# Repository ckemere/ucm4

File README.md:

# CM4-uSAW

Raspberry Pi Compute Module 4 micro carrier board with a multimodal Sensor Array and Wireless (uSAW) battery operation.

# Features

- Dual-camera inputs
- 9-axis IMU
- Stereo microphones
- GNSS module header (ZED GNSS)
- Stemma/QUIIC connector
- Power management
  - Battery charging & discharging
  - Fuel gauge
  - USB-C or L-ion power source
- SD card carrier
- UART Extension pins
- support for both Lite and eMMC variants of CM4
- USB C for power and USB 2.0 data transfer
- USB-OTG support

# Table of contents

1. [Sensors](sensors.md)

# License

This work is licensed under a [Creative Commons Attribution 4.0 International License][cc-by].

You can use it for anything as long as you preserve license file and author information in source distribution and authorship information on PCB. Derived work should mention original author in same locations as this repository.

[![CC BY 4.0][cc-by-image]][cc-by]

[cc-by]: http://creativecommons.org/licenses/by/4.0/
[cc-by-image]: https://i.creativecommons.org/l/by/4.0/88x31.png

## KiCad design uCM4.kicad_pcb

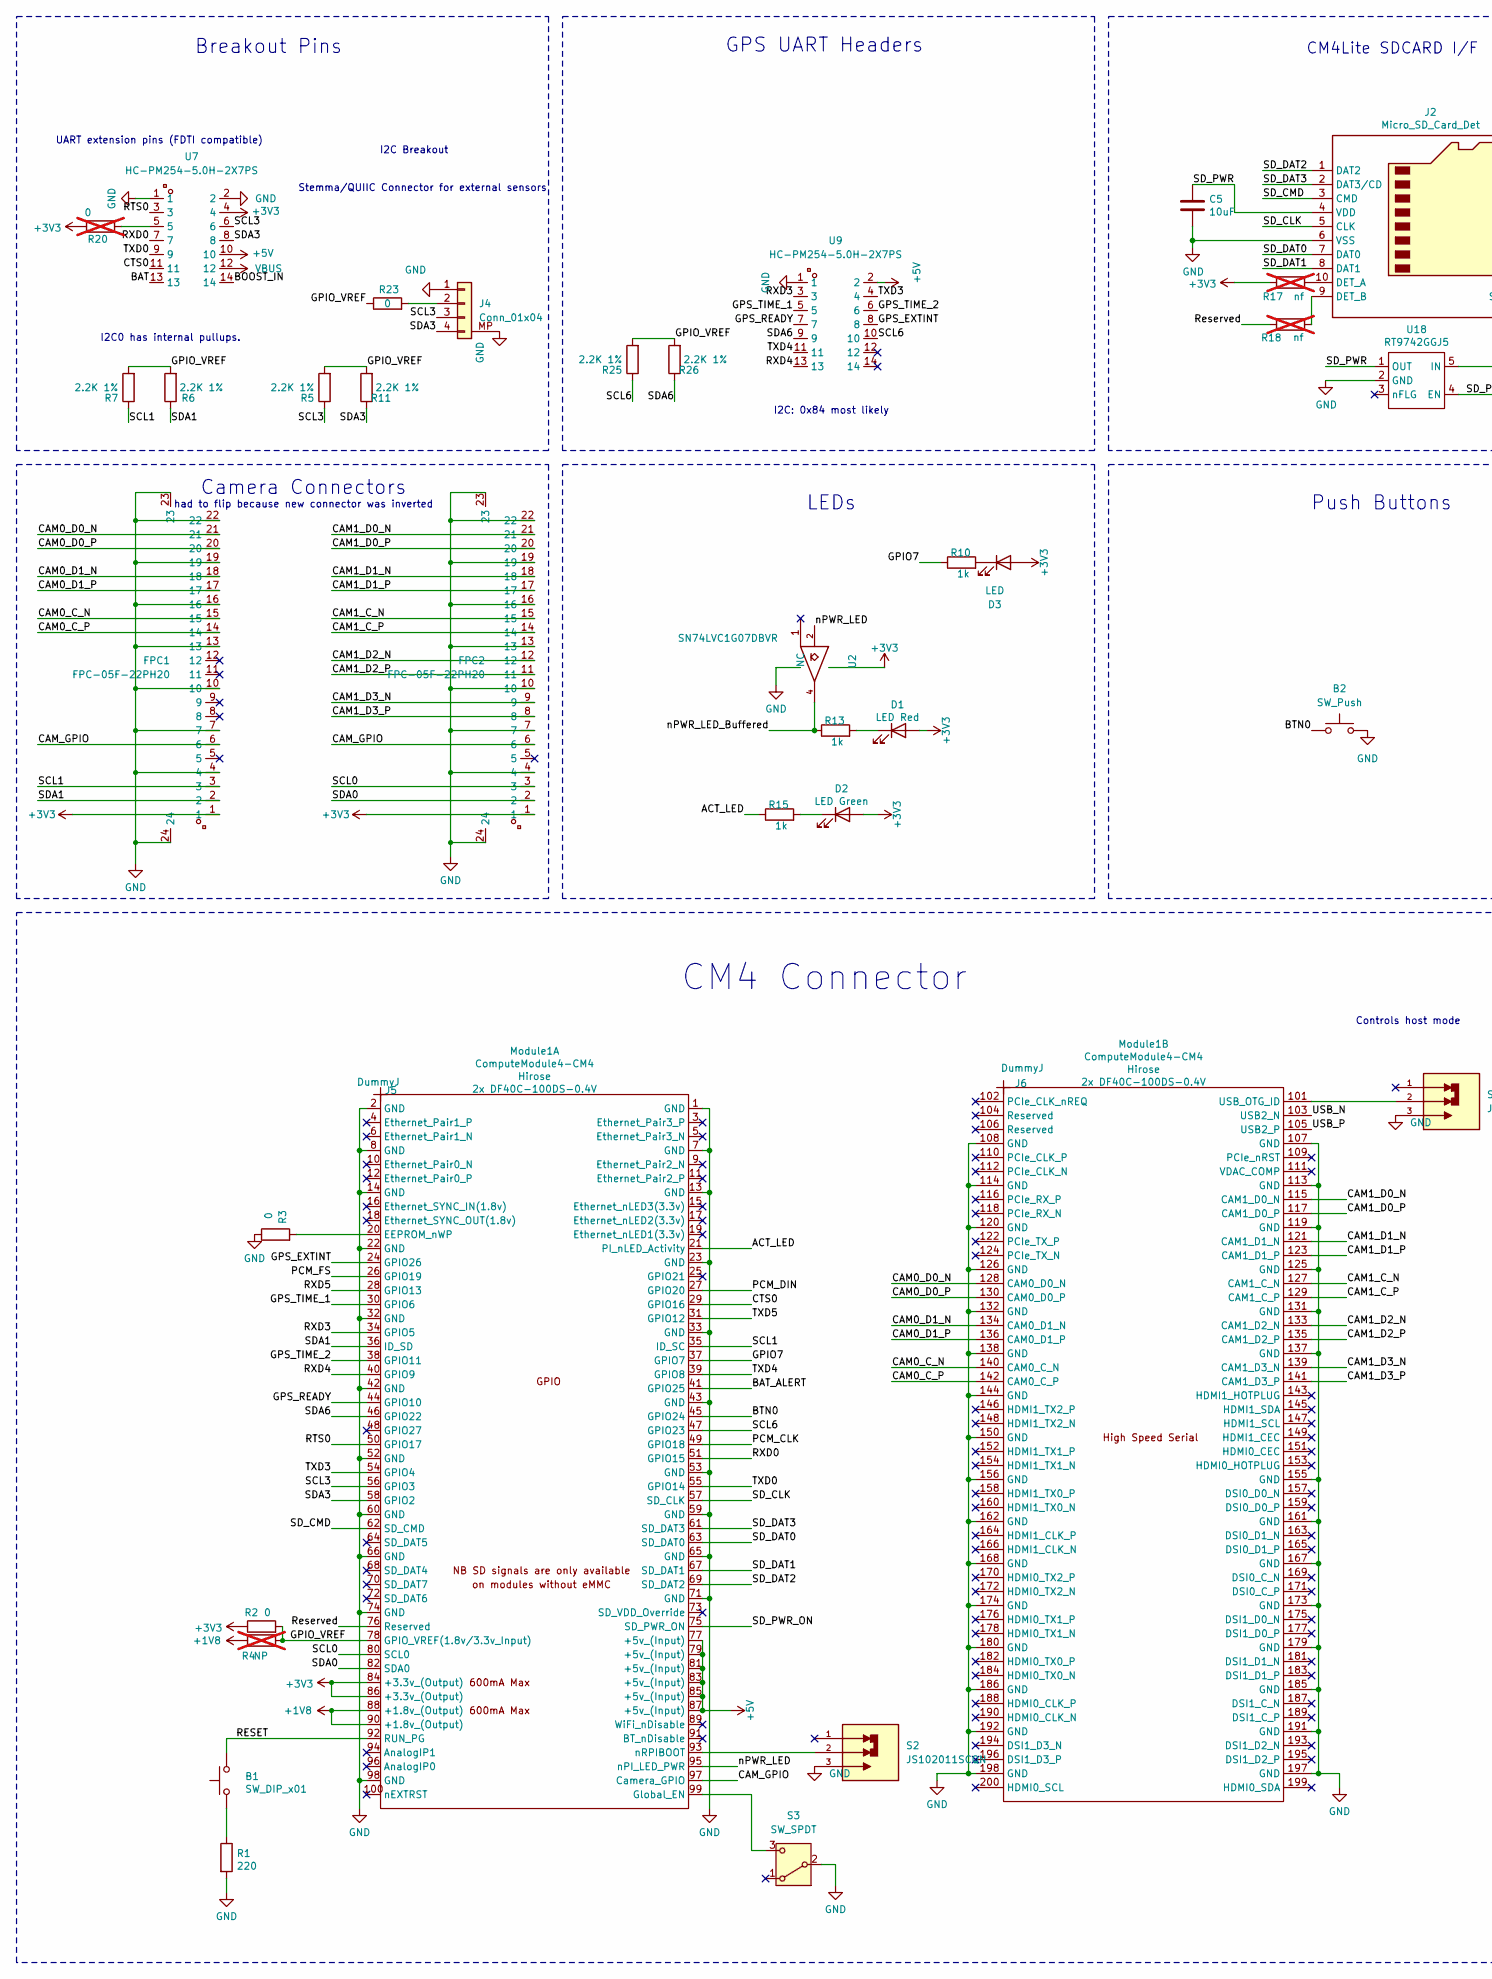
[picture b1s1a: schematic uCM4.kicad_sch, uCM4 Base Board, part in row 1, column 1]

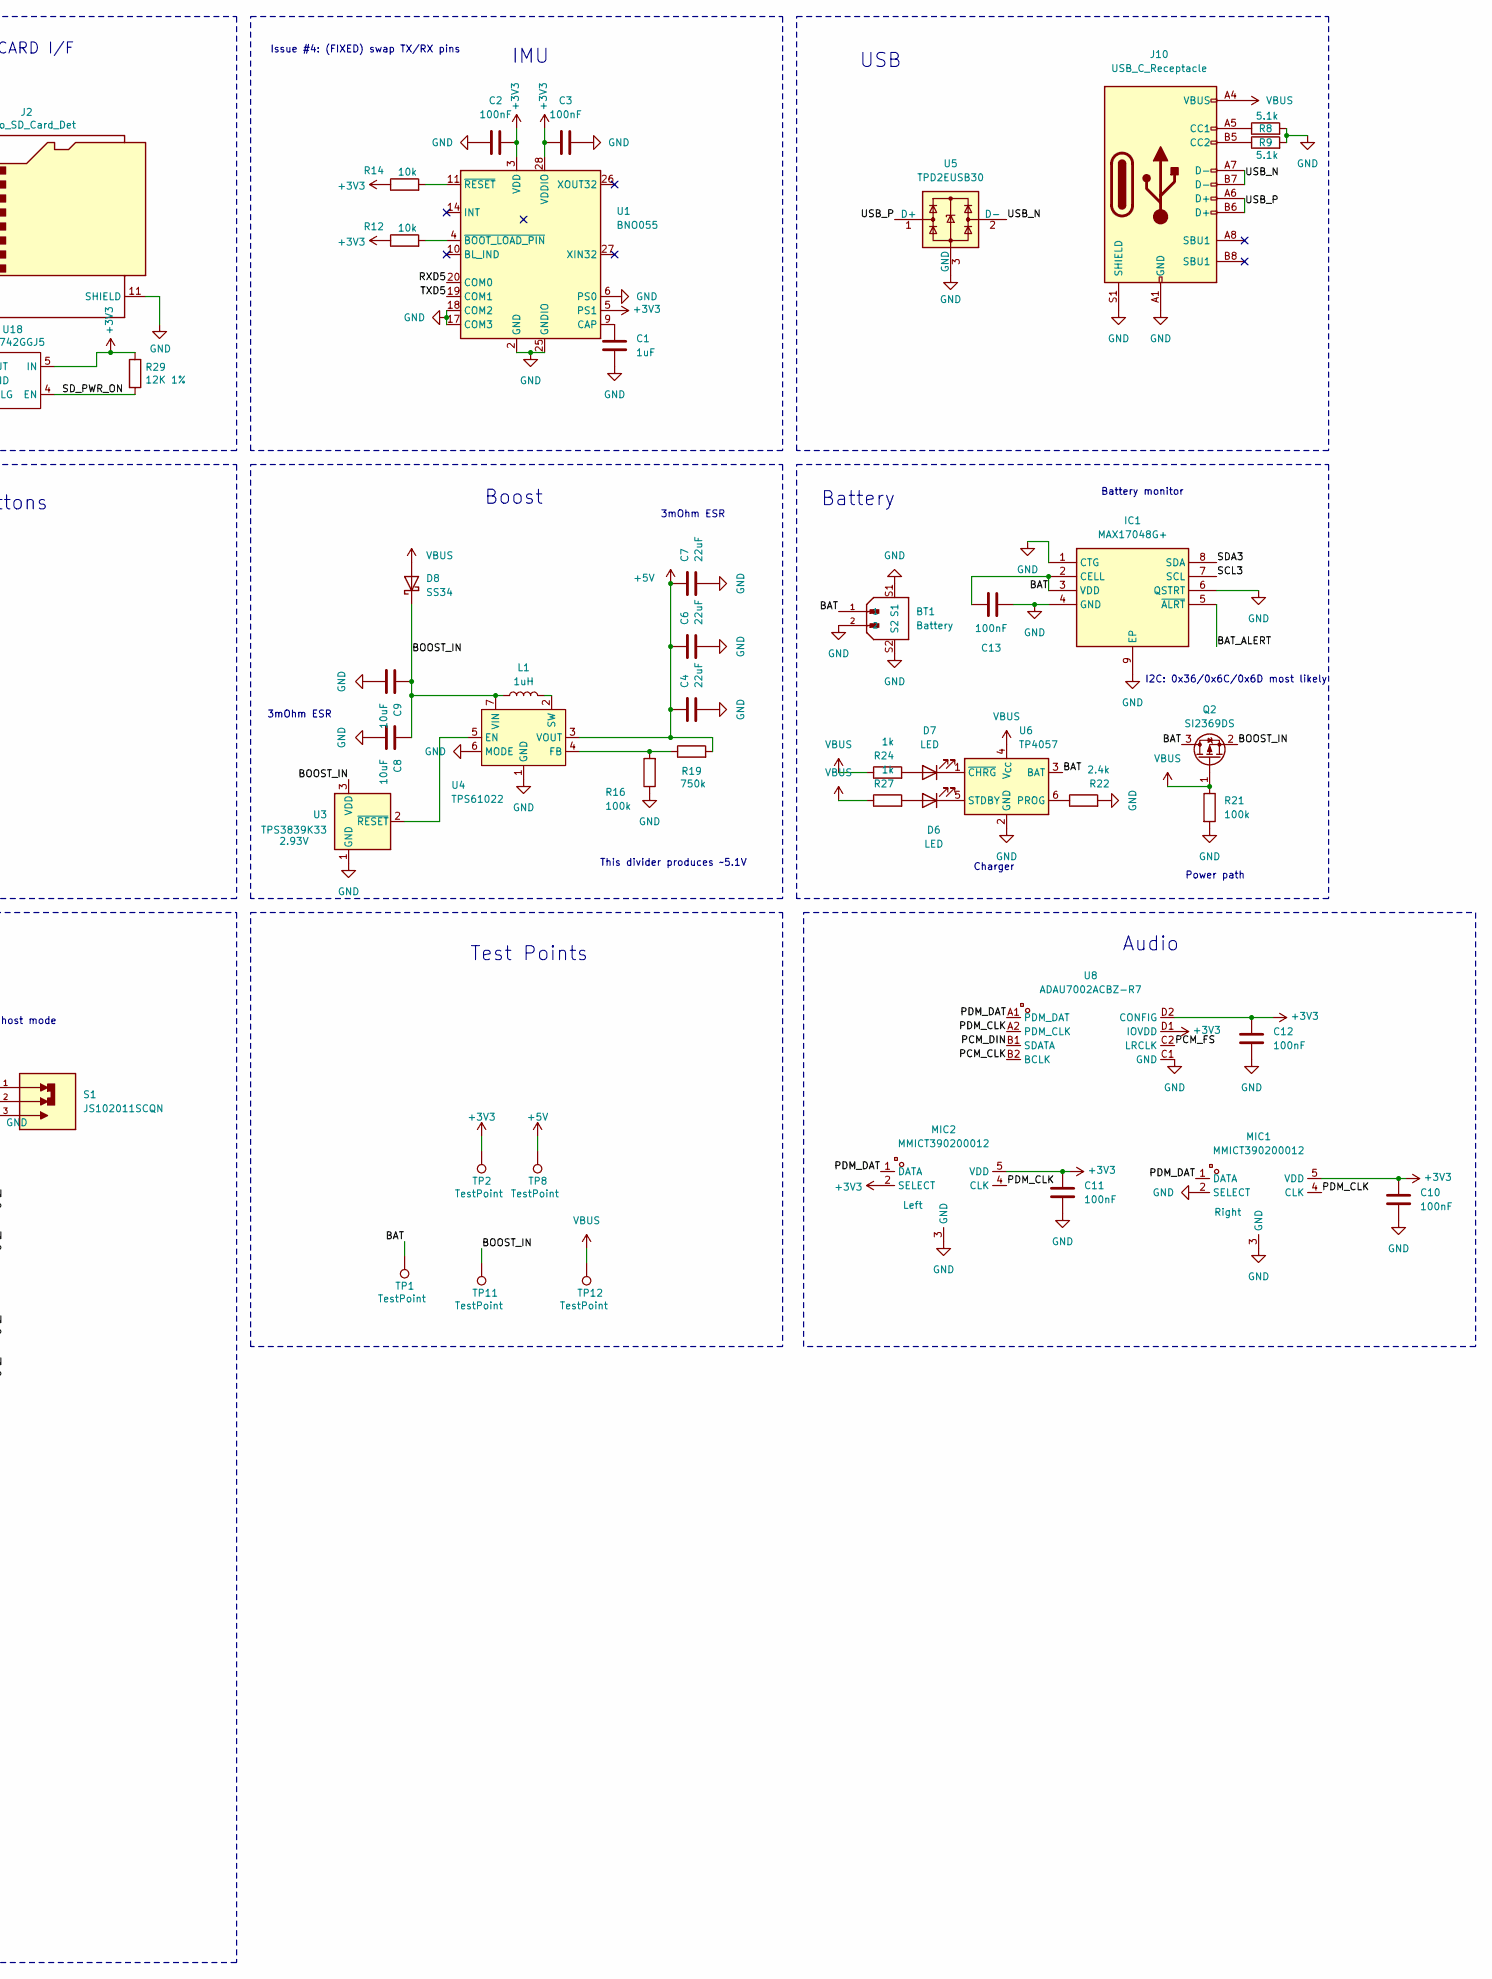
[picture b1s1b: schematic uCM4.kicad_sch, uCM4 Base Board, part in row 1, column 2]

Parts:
B1: SW_DIP_x01; PTS840_PM_SMTR_LFS; LCSC Part # C221907
B2: SW_Push; PTS840_PM_SMTR_LFS; LCSC Part # C221907
BT1: Battery; JST_B2B-PH-SM4-TB; PARTREV N/A; LCSC Part # C2763702
C1: 1uF; C_0402_1005Metric; LCSC Part # C14445
C2, C3, C10, C11, C12, C13: 100nF; C_0402_1005Metric; LCSC Part # C1525
C4, C6, C7: 22uF; C_1206_3216Metric; LCSC Part # C12891
C5: 10uF; C_0603_1608Metric; Part Description 10uF 10% 10V Ceramic Capacitor X7R 0805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; LCSC Part # C19702
C8, C9: 10uF; C_0603_1608Metric; LCSC Part # C19702
D1: LED Red; LED_0402_1005Metric; LCSC Part # C264407
D2: LED Green; LED_0402_1005Metric; LCSC Part # C5123485
D3, D6: LED; LED_0402_1005Metric; LCSC Part # C5123485
D7: LED; LED_0402_1005Metric; LCSC Part # C264407
D8: SS34; D_SMA; LCSC Part # C727059
FPC1, FPC2: FPC-05F-22PH20; FPC-SMD_22P-P0.50_FPC-05F-22PH20; LCSC Part C2856804
IC1: MAX17048G+; SON50P200X200X80-9N-D; Manufacturer_Part_Number MAX17048G+; Mouser Part Number 700-MAX17048G+
J2: Micro_SD_Card_Det; SDCARD_MOLEX_503398-1892; Part Description 9 (8 + 1) Position Card Connector micro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; LCSC Part # C428492
J4: Conn_01x04; JST_SH_BM04B-SRSS-TB_1x04-1MP_P1.00mm_Vertical; LCSC Part # C160390
J5, J6: DummyJ; LCSC Part # C597931
J10: USB_C_Receptacle; USB_C_Receptacle_GCT_USB4105-xx-A_16P_TopMnt_Horizontal; LCSC C5184243
L1: 1uH; XAL7030102MEC; Part# XAL7030-102MEC; LCSC Part # C19191626
MIC1, MIC2: MMICT390200012; MIC-SMD_5P-L3.5-W2.7-TL_MMICT390200012; LCSC Part C3171752
Module1: ComputeModule4-CM4; Raspberry-Pi-4-Compute-Module; LCSC Part # C597931
Q2: SI2369DS; SOT-23; LCSC Part # C41348108
R1: 220; R_0603_1608Metric_Pad0.98x0.95mm_HandSolder; LCSC Part # C22962
R2, R3, R23: 0; R_0402_1005Metric; LCSC Part # C106231
R4: NP; R_0402_1005Metric; LCSC Part # C106231; not fitted
R5, R6, R7, R11, R25, R26: 2.2K 1%; R_0402_1005Metric; Part Description Resistor 2.2K M1005 1% 63mW; LCSC Part # C60488
R8, R9: 5.1k; R_0402_1005Metric; LCSC Part # C25905
R10, R13, R15, R24, R27: 1k; R_0402_1005Metric; LCSC Part # C106235
R12, R14: 10k; R_0402_1005Metric; LCSC Part # C60490
R16, R21: 100k; R_0402_1005Metric; LCSC Part # C852472
R17, R18: nf; R_0402_1005Metric; Part Description Resistor 1K M1005 1% 63mW; not fitted
R19: 750k; R_0402_1005Metric; LCSC Part # C2909381
R20: 0; R_0402_1005Metric; LCSC Part # C21189; not fitted
R22: 2.4k; R_0402_1005Metric; LCSC Part # C25882
R29: 12K 1%; R_0402_1005Metric; Part Description Resistor 12K M1005 1% 63mW; LCSC Part # C25752
S1, S2: JS102011SCQN; SW_JS102011SCQN; PARTREV 8 Oct 21; LCSC Part # C221661
S3: SW_SPDT; SW_SPDT_PCM12; LCSC Part # C221841
TP1, TP2, TP8, TP11, TP12: TestPoint; TestPoint_Pad_D1.0mm
U1: BNO055; LGA-28_5.2x3.8mm_P0.5mm; LCSC Part # C93216
U2: SN74LVC1G07DBVR; SOT-23-5_HandSoldering; LCSC Part # C7829
U3: TPS3839DBZ; SOT-23; Threshold voltage 2.93V; Part_Code TPS3839K33; LCSC Part # C96333
U4: TPS61022; Texas_RWU0007A_VQFN-7_2x2mm_P0.5mm; LCSC Part # C915088
U5: TPD2EUSB30; Texas_DRT-3; LCSC Part # C3040102
U6: TP4057; TSOT-23-6; LCSC Part # C725791
U7, U9: HC-PM254-5.0H-2X7PS; HDR-SMD_14P-P2.54-V-F-R2-C7-LS7.4; LCSC Part # C42163135
U8: ADAU7002ACBZ-R7; WLCSP-8_L1.6-W0.8-R2-C4-P0.40-TL; LCSC Part C481886
U18: RT9742GGJ5; SOT-23-5; Part Description Power Switch/Driver 1:1 N-Channel 1A TS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; LCSC Part # C250547

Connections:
+1V8: Module1.88 (+1.8v_(Output)), Module1.90 (+1.8v_(Output)), R4.1
+3V3: C2.2, C3.2, C10.1, C11.1, C12.1, D1.2 (A), D2.2 (A), D3.2 (A), FPC1.1, FPC2.1, MIC1.5 (VDD), MIC2.2 (SELECT), MIC2.5 (VDD), Module1.84 (+3.3v_(Output)), Module1.86 (+3.3v_(Output)), R2.1, R12.1, R14.1, R17.1, R20.1, R29.1, TP2.1, U1.3 (VDD), U1.5 (PS1), U1.28 (VDDIO), U2.5 (VCC), U7.4, U8.D1 (IOVDD), U8.D2 (CONFIG), U18.5 (IN)
+5V: C4.1, C6.1, C7.1, Module1.77 (+5v_(Input)), Module1.79 (+5v_(Input)), Module1.81 (+5v_(Input)), Module1.83 (+5v_(Input)), Module1.85 (+5v_(Input)), Module1.87 (+5v_(Input)), R19.2, TP8.1, U4.3 (VOUT), U7.10, U9.2
/ACT_LED: Module1.21 (PI_nLED_Activity), R15.1
/BAT: BT1.1, C13.1, IC1.2 (CELL), IC1.3 (VDD), Q2.3 (D), TP1.1, U6.3 (BAT), U7.13
/BAT_ALERT: IC1.5 (~ALRT), Module1.41 (GPIO25)
/BOOST_IN: C8.1, C9.1, D8.1 (K), L1.1, Q2.2 (S), TP11.1, U3.3 (VDD), U4.7 (VIN), U7.14
/BTN0: B2.1, Module1.45 (GPIO24)
/CAM0_C_N: FPC1.15, Module1.140 (CAM0_C_N)
/CAM0_C_P: FPC1.14, Module1.142 (CAM0_C_P)
/CAM0_D0_N: FPC1.21, Module1.128 (CAM0_D0_N)
/CAM0_D0_P: FPC1.20, Module1.130 (CAM0_D0_P)
/CAM0_D1_N: FPC1.18, Module1.134 (CAM0_D1_N)
/CAM0_D1_P: FPC1.17, Module1.136 (CAM0_D1_P)
/CAM1_C_N: FPC2.15, Module1.127 (CAM1_C_N)
/CAM1_C_P: FPC2.14, Module1.129 (CAM1_C_P)
/CAM1_D0_N: FPC2.21, Module1.115 (CAM1_D0_N)
/CAM1_D0_P: FPC2.20, Module1.117 (CAM1_D0_P)
/CAM1_D1_N: FPC2.18, Module1.121 (CAM1_D1_N)
/CAM1_D1_P: FPC2.17, Module1.123 (CAM1_D1_P)
/CAM1_D2_N: FPC2.12, Module1.133 (CAM1_D2_N)
/CAM1_D2_P: FPC2.11, Module1.135 (CAM1_D2_P)
/CAM1_D3_N: FPC2.9, Module1.139 (CAM1_D3_N)
/CAM1_D3_P: FPC2.8, Module1.141 (CAM1_D3_P)
/CAM_GPIO: FPC1.6, FPC2.6, Module1.97 (Camera_GPIO)
/CTS0: Module1.29 (GPIO16), U7.11
/GPIO7: Module1.37 (GPIO7), R10.1
/GPIO_VREF: Module1.78 (GPIO_VREF(1.8v/3.3v_Input)), R2.2, R4.2, R5.2, R6.2, R7.2, R11.2, R23.1, R25.2, R26.2
/GPS_EXTINT: Module1.24 (GPIO26), U9.8
/GPS_READY: Module1.44 (GPIO10), U9.7
/GPS_TIME_1: Module1.30 (GPIO6), U9.5
/GPS_TIME_2: Module1.38 (GPIO11), U9.6
/PCM_CLK: Module1.49 (GPIO18), U8.B2 (BCLK)
/PCM_DIN: Module1.27 (GPIO20), U8.B1 (SDATA)
/PCM_FS: Module1.26 (GPIO19), U8.C2 (LRCLK)
/PDM_CLK: MIC1.4 (CLK), MIC2.4 (CLK), U8.A2 (PDM_CLK)
/PDM_DAT: MIC1.1 (DATA), MIC2.1 (DATA), U8.A1 (PDM_DAT)
/RESET: B1.2, Module1.92 (RUN_PG)
/RTS0: Module1.50 (GPIO17), U7.3
/RXD0: Module1.51 (GPIO15), U7.7
/RXD3: Module1.34 (GPIO5), U9.3
/RXD4: Module1.40 (GPIO9), U9.13
/RXD5: Module1.28 (GPIO13), U1.20 (COM0)
/Reserved: Module1.76 (Reserved), R18.1
/SCL0: FPC2.3, Module1.80 (SCL0)
/SCL1: FPC1.3, Module1.35 (ID_SC), R7.1
/SCL3: IC1.7 (SCL), J4.3, Module1.56 (GPIO3), R5.1, U7.6
/SCL6: Module1.47 (GPIO23), R25.1, U9.10
/SDA0: FPC2.2, Module1.82 (SDA0)
/SDA1: FPC1.2, Module1.36 (ID_SD), R6.1
/SDA3: IC1.8 (SDA), J4.4, Module1.58 (GPIO2), R11.1, U7.8
/SDA6: Module1.46 (GPIO22), R26.1, U9.9
/SD_CLK: J2.5 (CLK), Module1.57 (SD_CLK)
/SD_CMD: J2.3 (CMD), Module1.62 (SD_CMD)
/SD_DAT0: J2.7 (DAT0), Module1.63 (SD_DAT0)
/SD_DAT1: J2.8 (DAT1), Module1.67 (SD_DAT1)
/SD_DAT2: J2.1 (DAT2), Module1.69 (SD_DAT2)
/SD_DAT3: J2.2 (DAT3/CD), Module1.61 (SD_DAT3)
/SD_PWR: C5.1, J2.4 (VDD), U18.1 (OUT)
/SD_PWR_ON: Module1.75 (SD_PWR_ON), R29.2, U18.4 (EN)
/TXD0: Module1.55 (GPIO14), U7.9
/TXD3: Module1.54 (GPIO4), U9.4
/TXD4: Module1.39 (GPIO8), U9.11
/TXD5: Module1.31 (GPIO12), U1.19 (COM1)
/USB_N: J10.A7 (D-), J10.B7 (D-), Module1.103 (USB2_N), U5.2 (D-)
/USB_P: J10.A6 (D+), J10.B6 (D+), Module1.105 (USB2_P), U5.1 (D+)
/nPWR_LED: Module1.95 (nPI_LED_PWR), U2.2
/nPWR_LED_Buffered: R13.1, U2.4
GND: B2.2, BT1.2, BT1.S1, BT1.S2, C1.1, C2.1, C3.1, C4.2, C5.2, C6.2, C7.2, C8.2, C9.2, C10.2, C11.2, C12.2, C13.2, FPC1.4, FPC1.7, FPC1.10, FPC1.13, FPC1.16, FPC1.19, FPC1.22, FPC1.23, FPC1.24, FPC2.4, FPC2.7, FPC2.10, FPC2.13, FPC2.16, FPC2.19, FPC2.22, FPC2.23, FPC2.24, IC1.1 (CTG), IC1.4 (GND), IC1.6 (QSTRT), IC1.9 (EP), J2.6 (VSS), J2.11 (SHIELD), J4.1, J4.MP, J10.A1 (GND), J10.A12 (GND), J10.B1 (GND), J10.B12 (GND), J10.S1 (SHIELD), MIC1.2 (SELECT), MIC1.3 (GND), MIC2.3 (GND), Module1.1 (GND), Module1.2 (GND), Module1.7 (GND), Module1.8 (GND), Module1.13 (GND), Module1.14 (GND), Module1.22 (GND), Module1.23 (GND), Module1.32 (GND), Module1.33 (GND), Module1.42 (GND), Module1.43 (GND), Module1.52 (GND), Module1.53 (GND), Module1.59 (GND), Module1.60 (GND), Module1.65 (GND), Module1.66 (GND), Module1.71 (GND), Module1.74 (GND), Module1.98 (GND), Module1.107 (GND), Module1.108 (GND), Module1.113 (GND), Module1.114 (GND), Module1.119 (GND), Module1.120 (GND), Module1.125 (GND), Module1.126 (GND), Module1.131 (GND), Module1.132 (GND), Module1.137 (GND), Module1.138 (GND), Module1.144 (GND), Module1.150 (GND), Module1.155 (GND), Module1.156 (GND), Module1.161 (GND), Module1.162 (GND), Module1.167 (GND), Module1.168 (GND), Module1.173 (GND), Module1.174 (GND), Module1.179 (GND), Module1.180 (GND), Module1.185 (GND), Module1.186 (GND), Module1.191 (GND), Module1.192 (GND), Module1.197 (GND), Module1.198 (GND), R1.2, R3.1, R8.2, R9.2, R16.1, R21.2, R22.2, S1.3, S2.3, S3.2 (B), U1.2 (GND), U1.6 (PS0), U1.17 (COM3), U1.18 (COM2), U1.25 (GNDIO), U2.3 (GND), U3.1 (GND), U4.1 (GND), U4.6 (MODE), U5.3 (GND), U6.2 (GND), U7.1, U7.2, U8.C1 (GND), U9.1, U18.2 (GND)
unnamed: B1.1, R1.1
unnamed: D1.1 (K), R13.2
unnamed: D2.1 (K), R15.2
unnamed: D3.1 (K), R10.2
unnamed: D6.2 (A), R27.2
unnamed: D6.1 (K), U6.5 (STDBY)
unnamed: D7.2 (A), R24.2
unnamed: D7.1 (K), U6.1 (~CHRG)
unnamed: J2.10 (DET_A), R17.2
unnamed: J2.9 (DET_B), R18.2
unnamed: J4.2, R23.2
unnamed: J10.A5 (CC1), R8.1
unnamed: J10.B5 (CC2), R9.1
unnamed: Module1.20 (EEPROM_nWP), R3.2
unnamed: Module1.99 (Global_EN), S3.3 (C)
unnamed: Module1.93 (nRPIBOOT), S2.2
unnamed: Module1.101 (USB_OTG_ID), S1.2
unnamed: R20.2, U7.5
unnamed: C1.2, U1.9 (CAP)
unnamed: R12.2, U1.4 (~BOOT_LOAD_PIN)
unnamed: R14.2, U1.11 (~RESET)
unnamed: U3.2 (~RESET), U4.5 (EN)
unnamed: R16.2, R19.1, U4.4 (FB)
unnamed: L1.2, U4.2 (SW)
unnamed: R22.1, U6.6 (PROG)
VBUS: D8.2 (A), J10.A4 (VBUS), J10.A9 (VBUS), J10.B4 (VBUS), J10.B9 (VBUS), Q2.1 (G), R21.1, R24.1, R27.1, TP12.1, U6.4 (V_{CC}), U7.12

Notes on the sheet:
CM4 Connector
Battery monitor
3mOhm ESR
Test Points
Push Buttons
I2C: 0x84 most likely
Battery
CM4Lite SDCARD I/F
Controls host mode
had to flip because new connector was inverted
GPS UART Headers
This divider produces ~5.1V
UART extension pins (FDTI compatible)
IMU
USB
I2C Breakout
LEDs
Audio
Boost
Power path
Charger
Stemma/QUIIC Connector for external sensors
Issue #4: (FIXED) swap TX/RX pins
Camera Connectors
I2C: 0x36/0x6C/0x6D most likely
Breakout Pins
I2C0 has internal pullups.

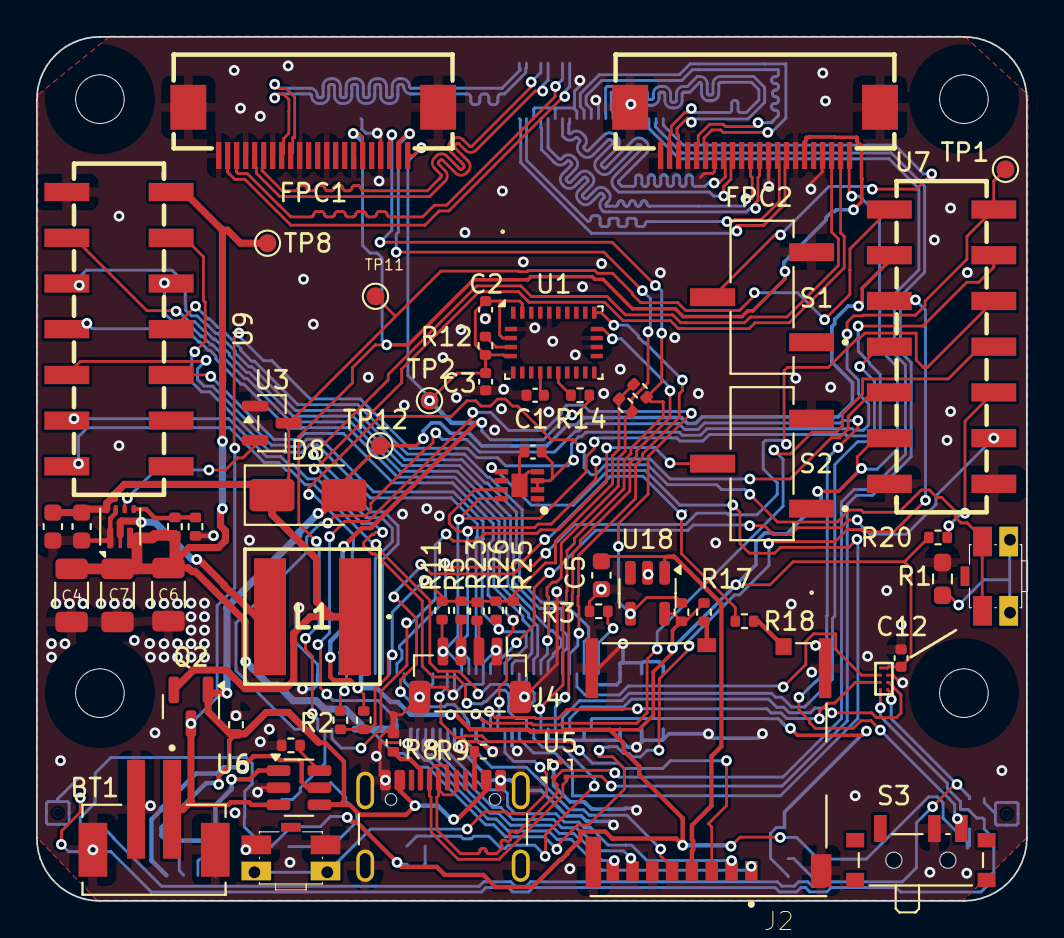
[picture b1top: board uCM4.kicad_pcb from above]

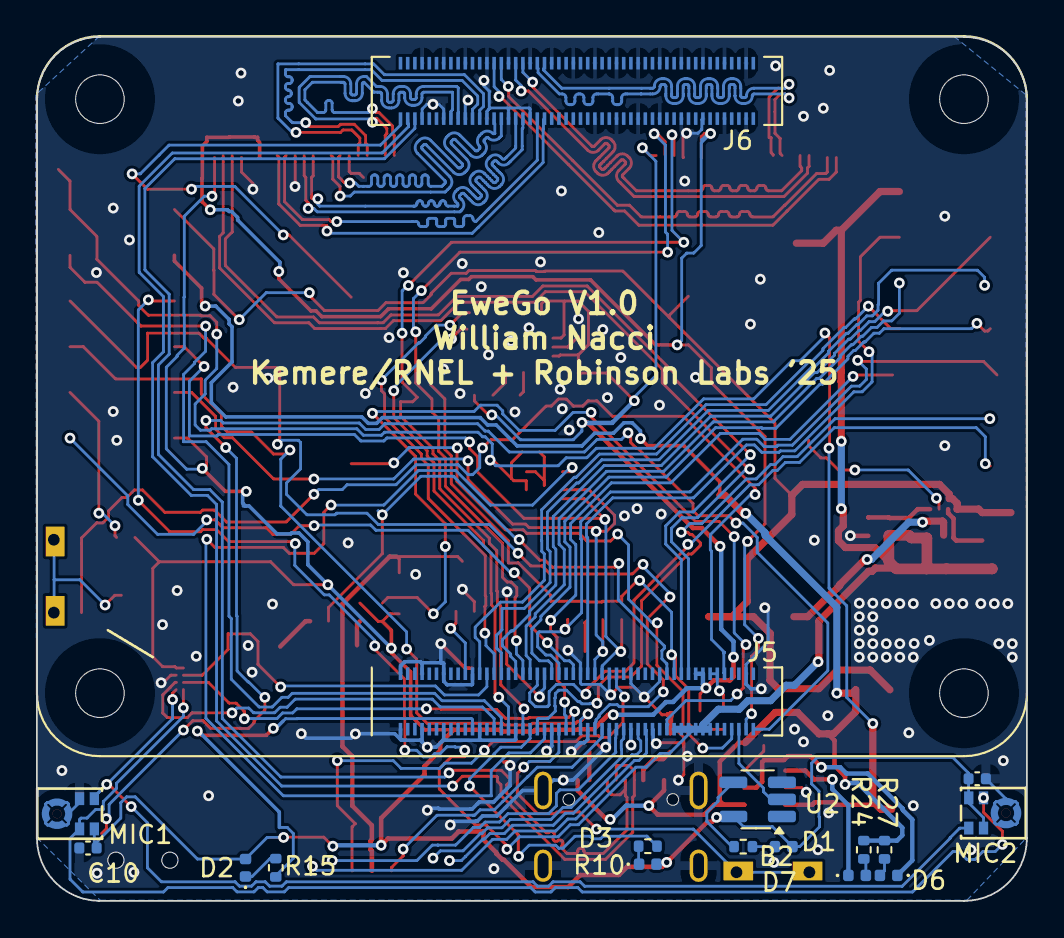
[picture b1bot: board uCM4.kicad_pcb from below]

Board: 2 copper layers, 55.0 x 48.0 mm, 81 parts (18 on the bottom side), 95 nets.

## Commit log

2025-12-04 Editing models & etc. (oops?) Importing camera connectors.
2025-12-04 Removed ethernet connector
2025-12-04 Cameras added in sch.
2025-12-04 Added text
2025-12-05 Adding different camera connectors
2025-12-05 Adding vertical cam connectors
2025-12-07 Revert "Added text"
    This reverts commit 62975cc76e4f780cb44087bac7d1ba26b0b1c88f.
2025-12-07 Reapply "Added text"
    This reverts commit ba47ba2ab880adebf2a51512258938aba623be2e.
2025-12-07 Revert "Adding vertical cam connectors"
    This reverts commit 5f1061bc0e5e73f1cfbd759f8bf3abef7a074a53.
2025-12-07 Revert "Adding different camera connectors"
    This reverts commit 13c594ec966e128ca79b7e90b630a66479b00dc6.
2025-12-07 Adding UART pins and changing connectors.
2025-12-07 Added GPS UART to sch
2025-12-07 Added IMU
2025-12-07 Added battery boost, reorganized schematic.
2025-12-07 Adding 3d models and arranging board
2025-12-07 PCB Arrangement
2025-12-07 Added environmental sensor.
2025-12-08 Changing connectors and arranging PCB.
2025-12-08 Changing models & some initial routing
2025-12-09 Added STEMMA connector and some comments
2025-12-09 Added fuel gauge + USB C + some other things
2025-12-09 Adding battery charging circuitry.
2025-12-09 Removing onboard environmental sensor.
2025-12-09 Rearrangements
2025-12-10 Changed some parts and hopeful final PCB arrangement.
2025-12-11 Moving LEDs
2025-12-11 Changed resistors to 0402
2025-12-11 Changed capacitor sizes
2025-12-11 Updated USB-C connector to be simpler.
2025-12-11 Arranging and changing switches.
2025-12-11 Routing
2025-12-12 Correcting symbols and routing progress.
2025-12-12 Updating LCSC numbers.
2025-12-12 Minor changes
2025-12-12 Tuning differential traces and changing some footprints
2025-12-12 Finalized LCSC selections
2025-12-13 Prepping for production.
2025-12-13 Updated comments.
2026-01-16 Adding github issues. Almost completed in schematic.
2026-01-16 Fixed switches.
2026-01-16 Board fixes. Fixed PMU (via UVLO via voltage monitor for buck) changed I2C lines, FET replacment, etc. Issues listed as 'Issue' comments on schematic.
2026-01-17 Adding new parts to the project, fixing a number of issues on board, adding audio interface.
2026-01-17 Added new camera connectors. (Had to flip the symbol to match up hirose connection order)
2026-01-17 Routing in progress
2026-01-17 Routed and should be ready to order
2026-01-18 Routed first camera (with proper length matching this time)
2026-01-18 Second camera routed (with proper trace lengths this time!)
2026-01-18 DRC checked.
2026-01-18 Switched camera I2Cs to match official RPi documentation.
2026-01-18 Cleared issue messages.
2026-01-18 Production ready files.
2026-02-06 Added voltage label to monitor.
2026-02-10 Moved component files to subdirectory and fixed/improved some 3d models
2026-02-10 Footprint change
2026-02-10 Renamed project.
2026-02-11 More detail on sensor configs.
